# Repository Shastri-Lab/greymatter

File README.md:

# greymatter DAC controller

Embedded firmware for the Raspberry Pi Pico 2 (RP2350) controlling a multi-board DAC system for precision analog output generation. Designed for photonic neural network research applications.

## Features

- **24 DAC Control**: 8 daughter boards, each with 3 DACs (2x current, 1x voltage)
- **High Channel Count**: 112 current outputs + 32 voltage outputs = 144 total channels
- **SCPI Interface**: Standard instrument control commands over USB serial
- **Precision Output**:
  - Current: 3.125 mA to 300 mA full-scale (LTC2662)
  - Voltage: ±2.5V to ±10V bipolar, 0-10V unipolar (LTC2664)
- **16-bit Resolution**: 65,536 steps per channel
- **Fault Monitoring**: Per-DAC fault detection with interrupt support

## Hardware Requirements

- Raspberry Pi Pico 2 (RP2350)
- Greymatter motherboard with:
  - 3x MCP23S17 I/O expanders
  - TXB0106 level shifter
  - 8 daughter board slots
- Microcyte daughter boards (per slot):
  - 2x LTC2662 current DAC (5 channels each)
  - 1x LTC2664 voltage DAC (4 channels)

## Quick Start

### Prerequisites

```bash
# Set Pico SDK path
export PICO_SDK_PATH=/path/to/pico-sdk

# Required tools
# - CMake 3.13+
# - GCC ARM cross-compiler (gcc-15 recommended)
```

### Build

```bash
cd build
cmake .. -DPICO_BOARD=pico2
make picotoolBuild
C_INCLUDE_PATH= CPLUS_INCLUDE_PATH= make

# Optional: Custom SPI clock rate (default 10 MHz)
cmake .. -DPICO_BOARD=pico2 -DSPI_BAUDRATE=1000000  # 1 MHz for logic analyzer
make picotoolBuild && C_INCLUDE_PATH= CPLUS_INCLUDE_PATH= make
```

### Flash

1. Hold the **BOOTSEL** button on the Pico 2
2. Connect USB cable to computer
3. Copy `build/greymatter.uf2` to the `RPI-RP2` drive that appears
4. The Pico will reset and start running automatically

### Connect

```bash
# macOS/Linux
screen /dev/tty.usbmodem1101 115200

# Exit screen: Ctrl-A, K, Y
```

### Verify

```
*IDN?
```
Response: `greymatter,DAC Controller,001,0.1`

## Basic Usage

```bash
# Set voltage output (Board 0, DAC 2, Channel 0 to 5V)
BOARD0:DAC2:CH0:VOLT 5.0

# Set current output (Board 0, DAC 0, Channel 1 to 50mA)
BOARD0:DAC0:CH1:CURR 50.0

# Check for faults
FAULT?

# Reset all outputs
*RST
```

## Documentation

The **[user guide](docs/USER_GUIDE.md)** for the firmware contains a complete command reference, implementation details, calibration routines, and more details.

## Architecture

```
┌─────────────────────────────────────────────────────────────┐
│                     USB Serial (115200 baud)                │
└─────────────────────────────────────────────────────────────┘
                              │
                              ▼
┌─────────────────────────────────────────────────────────────┐
│                     SCPI Parser                             │
│              Command tokenization & validation              │
└─────────────────────────────────────────────────────────────┘
                              │
                              ▼
┌─────────────────────────────────────────────────────────────┐
│                     Board Manager                           │
│              Routes commands to 24 DACs                     │
└─────────────────────────────────────────────────────────────┘
                              │
              ┌───────────────┴───────────────┐
              ▼                               ▼
┌──────────────────────┐         ┌──────────────────────┐
│      LTC2662         │         │      LTC2664         │
│  Current DAC Driver  │         │  Voltage DAC Driver  │
│  (5 ch, 3-300 mA)    │         │  (4 ch, ±10V)        │
└──────────────────────┘         └──────────────────────┘
              │                               │
              └───────────────┬───────────────┘
                              ▼
┌─────────────────────────────────────────────────────────────┐
│                     SPI Manager                             │
│              Transaction coordination                       │
└─────────────────────────────────────────────────────────────┘
                              │
              ┌───────────────┴───────────────┐
              ▼                               ▼
┌──────────────────────┐         ┌──────────────────────┐
│    I/O Expanders     │         │    DAC Decoder       │
│  (MCP23S17 × 3)      │         │    (CS routing)      │
└──────────────────────┘         └──────────────────────┘
```

## Pin Assignments

| GPIO | Function | Description |
|------|----------|-------------|
| GP16 | SPI_MISO | Data from DACs/expanders |
| GP17 | SPI_CS | Chip select (expanders only) |
| GP18 | SPI_CLK | SPI clock (configurable, default 10 MHz) |
| GP19 | SPI_MOSI | Data to DACs/expanders |
| GP20 | FAULT | Combined fault input |
| GP21 | LEVEL_SHIFT_OE | Level shifter enable |
| GP22 | EXPANDER_RESET | I/O expander reset |

## Project Structure

```
greymatter/
├── main.cpp              # Entry point, USB serial loop
├── scpi_parser.*         # SCPI command parsing
├── board_manager.*       # DAC routing and management
├── spi_manager.*         # SPI peripheral control
├── io_expander.*         # MCP23S17 driver
├── dac_device.*          # Abstract DAC interface
├── ltc2662.*             # Current DAC driver
├── ltc2664.*             # Voltage DAC driver
├── utils.*               # String parsing utilities
├── CMakeLists.txt        # Build configuration
├── docs/                 # Hardware programming guides
├── README.md             # This file
└── USER_GUIDE.md         # Detailed user documentation
```

## License
This software is licensed under the MIT license found at [LICENSE](LICENSE).

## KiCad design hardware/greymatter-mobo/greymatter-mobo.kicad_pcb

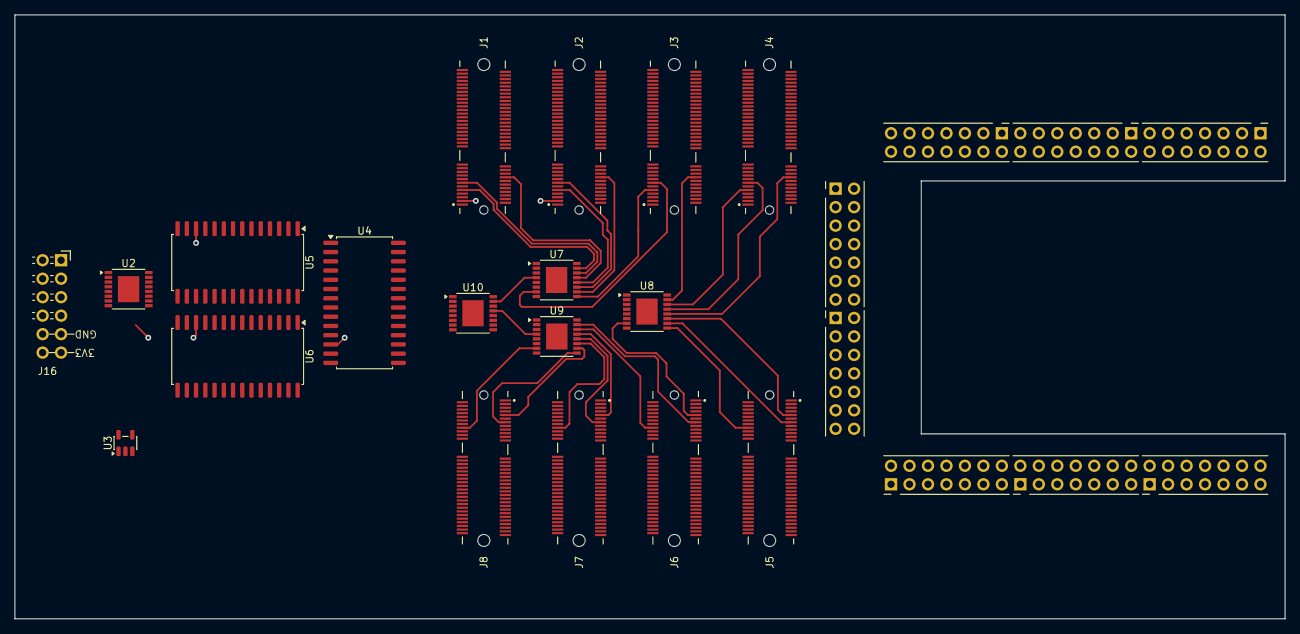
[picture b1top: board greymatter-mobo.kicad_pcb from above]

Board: 6 copper layers, 174.6 x 83.0 mm, 18 parts (0 on the bottom side), 79 nets.

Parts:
J1, J2, J3, J4, J5, J6, J7, J8: M2-J-67-V-SMT-5.30-KE-KT; ADAMTECH_M2-J-67-V-SMT-5.30-KE-KT
J16: Conn_01x12; PinHeader_2x06_PMOD_Peripheral
U2: TXB0106RGYR; TSSOP-16-1EP_4.4x5mm_P0.65mm
U3: 74LVC1G32; SOT-23-5
U4, U5, U6: MCP23S17_SO; SOIC-28W_7.5x17.9mm_P1.27mm
U7, U8, U9, U10: SN74LVC138ARGYR; TSSOP-16-1EP_4.4x5mm_P0.65mm

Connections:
+3V3: J16.6, J16.12, U2.2 (VCCA)
+5V: J1.4, J1.21, J2.4, J2.21, J3.4, J3.21, J4.4, J4.21, J5.4, J5.21, J6.4, J6.21, J7.4, J7.21, J8.4, J8.21, U2.15 (VCCB), U3.5 (VCC), U4.9 (VDD), U5.9 (VDD), U5.15 (A0), U6.9 (VDD), U6.16 (A1), U7.6 (G1), U7.16 (VCC), U8.6 (G1), U8.16 (VCC), U9.6 (G1), U9.16 (VCC), U10.16 (VCC)
+10V: J1.34, J1.35, J1.36, J1.37, J2.34, J2.35, J2.36, J2.37, J3.34, J3.35, J3.36, J3.37, J4.34, J4.35, J4.36, J4.37, J5.34, J5.35, J5.36, J5.37, J6.34, J6.35, J6.36, J6.37, J7.34, J7.35, J7.36, J7.37, J8.34, J8.35, J8.36, J8.37
-10V: J1.70, J1.71, J1.72, J1.73, J2.70, J2.71, J2.72, J2.73, J3.70, J3.71, J3.72, J3.73, J4.70, J4.71, J4.72, J4.73, J5.70, J5.71, J5.72, J5.73, J6.70, J6.71, J6.72, J6.73, J7.70, J7.71, J7.72, J7.73, J8.70, J8.71, J8.72, J8.73
CLRDAC: J1.10, J2.10, J3.10, J4.10, J5.10, J6.10, J7.10, J8.10
CS: U2.16 (B1), U4.11 (~CS), U5.11 (~CS), U6.11 (~CS), U10.6 (G1)
CS0: U4.25 (GPA4), U7.1 (A), U8.1 (A), U9.1 (A)
CS1: U4.24 (GPA3), U7.2 (B), U8.2 (B), U9.2 (B)
CS2: U4.23 (GPA2), U7.3 (C), U8.3 (C), U9.3 (C)
CS3: U4.22 (GPA1), U10.1 (A)
CS4: U4.21 (GPA0), U10.2 (B)
CS_3V3: J16.1, U2.1 (A1)
CS_11: J1.7, U7.15 (Y0)
CS_12: J1.5, U7.14 (Y1)
CS_13: J1.3, U7.13 (Y2)
CS_21: J2.7, U7.12 (Y3)
CS_22: J2.5, U7.11 (Y4)
CS_23: J2.3, U7.10 (Y5)
CS_31: J3.7, U7.9 (Y6)
CS_32: J3.5, U7.7 (Y7)
CS_33: J3.3, U8.15 (Y0)
CS_41: J4.7, U8.14 (Y1)
CS_42: J4.5, U8.13 (Y2)
CS_43: J4.3, U8.12 (Y3)
CS_51: J5.7, U8.11 (Y4)
CS_52: J5.5, U8.10 (Y5)
CS_53: J5.3, U8.9 (Y6)
CS_61: J6.7, U8.7 (Y7)
CS_62: J6.5, U9.15 (Y0)
CS_63: J6.3, U9.14 (Y1)
CS_71: J7.7, U9.13 (Y2)
CS_72: J7.5, U9.12 (Y3)
CS_73: J7.3, U9.11 (Y4)
CS_81: J8.7, U9.10 (Y5)
CS_82: J8.5, U9.9 (Y6)
CS_83: J8.3, U9.7 (Y7)
DAC_FAULT: U3.2, U5.20 (INTA)
DEN: U4.26 (GPA5), U7.5 (*G2B), U8.5 (*G2B), U9.5 (*G2B)
D_EN0: U7.4 (*G2A), U10.15 (Y0)
D_EN1: U8.4 (*G2A), U10.14 (Y1)
D_EN2: U9.4 (*G2A), U10.13 (Y2)
FAULT: U2.10 (B6), U3.4
FAULT_3V3: J16.7, U2.7 (A6)
FAULT_11: J1.19, U5.21 (GPA0)
FAULT_12: J1.18, U5.22 (GPA1)
FAULT_21: J2.19, U5.23 (GPA2)
FAULT_22: J2.18, U5.24 (GPA3)
FAULT_31: J3.19, U5.25 (GPA4)
FAULT_32: J3.18, U5.26 (GPA5)
FAULT_41: J4.19, U5.27 (GPA6)
FAULT_42: J4.18, U5.28 (GPA7)
FAULT_51: J5.19, U5.1 (GPB0)
FAULT_52: J5.18, U5.2 (GPB1)
FAULT_61: J6.19, U5.3 (GPB2)
FAULT_62: J6.18, U5.4 (GPB3)
FAULT_71: J7.19, U5.5 (GPB4)
FAULT_72: J7.18, U5.6 (GPB5)
FAULT_81: J8.19, U5.7 (GPB6)
FAULT_82: J8.18, U5.8 (GPB7)
GND: J1.1, J1.2, J1.8, J1.11, J1.13, J1.14, J1.15, J1.17, J1.22, J1.23, J1.32, J1.33, J1.38, J1.39, J1.40, J1.41, J1.44, J1.45, J1.48, J1.49, J1.52, J1.53, J1.56, J1.57, J1.60, J1.61, J1.64, J1.65, J1.68, J1.69, J1.74, J1.75, J2.1, J2.2, J2.8, J2.11, J2.13, J2.14, J2.15, J2.17, J2.22, J2.23, J2.32, J2.33, J2.38, J2.39, J2.40, J2.41, J2.44, J2.45, J2.48, J2.49, J2.52, J2.53, J2.56, J2.57, J2.60, J2.61, J2.64, J2.65, J2.68, J2.69, J2.74, J2.75, J3.1, J3.2, J3.8, J3.11, J3.13, J3.14, J3.15, J3.17, J3.22, J3.23, J3.32, J3.33, J3.38, J3.39, J3.40, J3.41, J3.44, J3.45, J3.48, J3.49, J3.52, J3.53, J3.56, J3.57, J3.60, J3.61, J3.64, J3.65, J3.68, J3.69, J3.74, J3.75, J4.1, J4.2, J4.8, J4.11, J4.13, J4.14, J4.15, J4.17, J4.22, J4.23, J4.32, J4.33, J4.38, J4.39, J4.40, J4.41, J4.44, J4.45, J4.48, J4.49, J4.52, J4.53, J4.56, J4.57, J4.60, J4.61, J4.64, J4.65, J4.68, J4.69, J4.74, J4.75, J5.1, J5.2, J5.8, J5.11, J5.13, J5.14, J5.15, J5.17, J5.22, J5.23, J5.32, J5.33, J5.38, J5.39, J5.40, J5.41, J5.44, J5.45, J5.48, J5.49, J5.52, J5.53, J5.56, J5.57, J5.60, J5.61, J5.64, J5.65, J5.68, J5.69, J5.74, J5.75, J6.1, J6.2, J6.8, J6.11, J6.13, J6.14, J6.15, J6.17, J6.22, J6.23, J6.32, J6.33, J6.38, J6.39, J6.40, J6.41, J6.44, J6.45, J6.48, J6.49, J6.52, J6.53, J6.56, J6.57, J6.60, J6.61, J6.64, J6.65, J6.68, J6.69, J6.74, J6.75, J7.1, J7.2, J7.8, J7.11, J7.13, J7.14, J7.15, J7.17, J7.22, J7.23, J7.32, J7.33, J7.38, J7.39, J7.40, J7.41, J7.44, J7.45, J7.48, J7.49, J7.52, J7.53, J7.56, J7.57, J7.60, J7.61, J7.64, J7.65, J7.68, J7.69, J7.74, J7.75, J8.1, J8.2, J8.8, J8.11, J8.13, J8.14, J8.15, J8.17, J8.22, J8.23, J8.32, J8.33, J8.38, J8.39, J8.40, J8.41, J8.44, J8.45, J8.48, J8.49, J8.52, J8.53, J8.56, J8.57, J8.60, J8.61, J8.64, J8.65, J8.68, J8.69, J8.74, J8.75, J16.5, J16.11, U2.9 (GND), U2.17 (EPAD), U3.3 (GND), U4.10 (VSS), U4.15 (A0), U4.16 (A1), U4.17 (A2), U5.10 (VSS), U5.16 (A1), U5.17 (A2), U6.10 (VSS), U6.15 (A0), U6.17 (A2), U7.8 (GND), U7.17 (EPAD), U8.8 (GND), U8.17 (EPAD), U9.8 (GND), U9.17 (EPAD), U10.3 (C), U10.4 (*G2A), U10.5 (*G2B), U10.8 (GND), U10.17 (EPAD)
LDAC: J1.16, J2.16, J3.16, J4.16, J5.16, J6.16, J7.16, J8.16, U4.1 (GPB0)
MISO: J1.6, J2.6, J3.6, J4.6, J5.6, J6.6, J7.6, J8.6, U2.12 (B4), U4.14 (SO), U5.14 (SO), U6.14 (SO)
MISO_3V3: J16.3, U2.5 (A4)
MOSI: J1.9, J2.9, J3.9, J4.9, J5.9, J6.9, J7.9, J8.9, U2.13 (B3), U4.13 (SI), U5.13 (SI), U6.13 (SI)
MOSI_3V3: J16.2, U2.4 (A3)
OE_3V3: J16.9, U2.8 (OE)
RESET: U2.11 (B5), U4.18 (~RESET), U5.18 (~RESET), U6.18 (~RESET)
RESET_3V3: J16.8, U2.6 (A5)
SCK_3V3: J16.4, U2.3 (A2)
SCLK: J1.12, J2.12, J3.12, J4.12, J5.12, J6.12, J7.12, J8.12, U2.14 (B2), U4.12 (SCK), U5.12 (SCK), U6.12 (SCK)
TEMP1: J1.20, U6.21 (GPA0)
TEMP2: J2.20, U6.22 (GPA1)
TEMP3: J3.20, U6.23 (GPA2)
TEMP4: J4.20, U6.24 (GPA3)
TEMP5: J5.20, U6.25 (GPA4)
TEMP6: J6.20, U6.26 (GPA5)
TEMP7: J7.20, U6.27 (GPA6)
TEMP8: J8.20, U6.28 (GPA7)
TEMP_FAULT: U3.1, U6.20 (INTA)

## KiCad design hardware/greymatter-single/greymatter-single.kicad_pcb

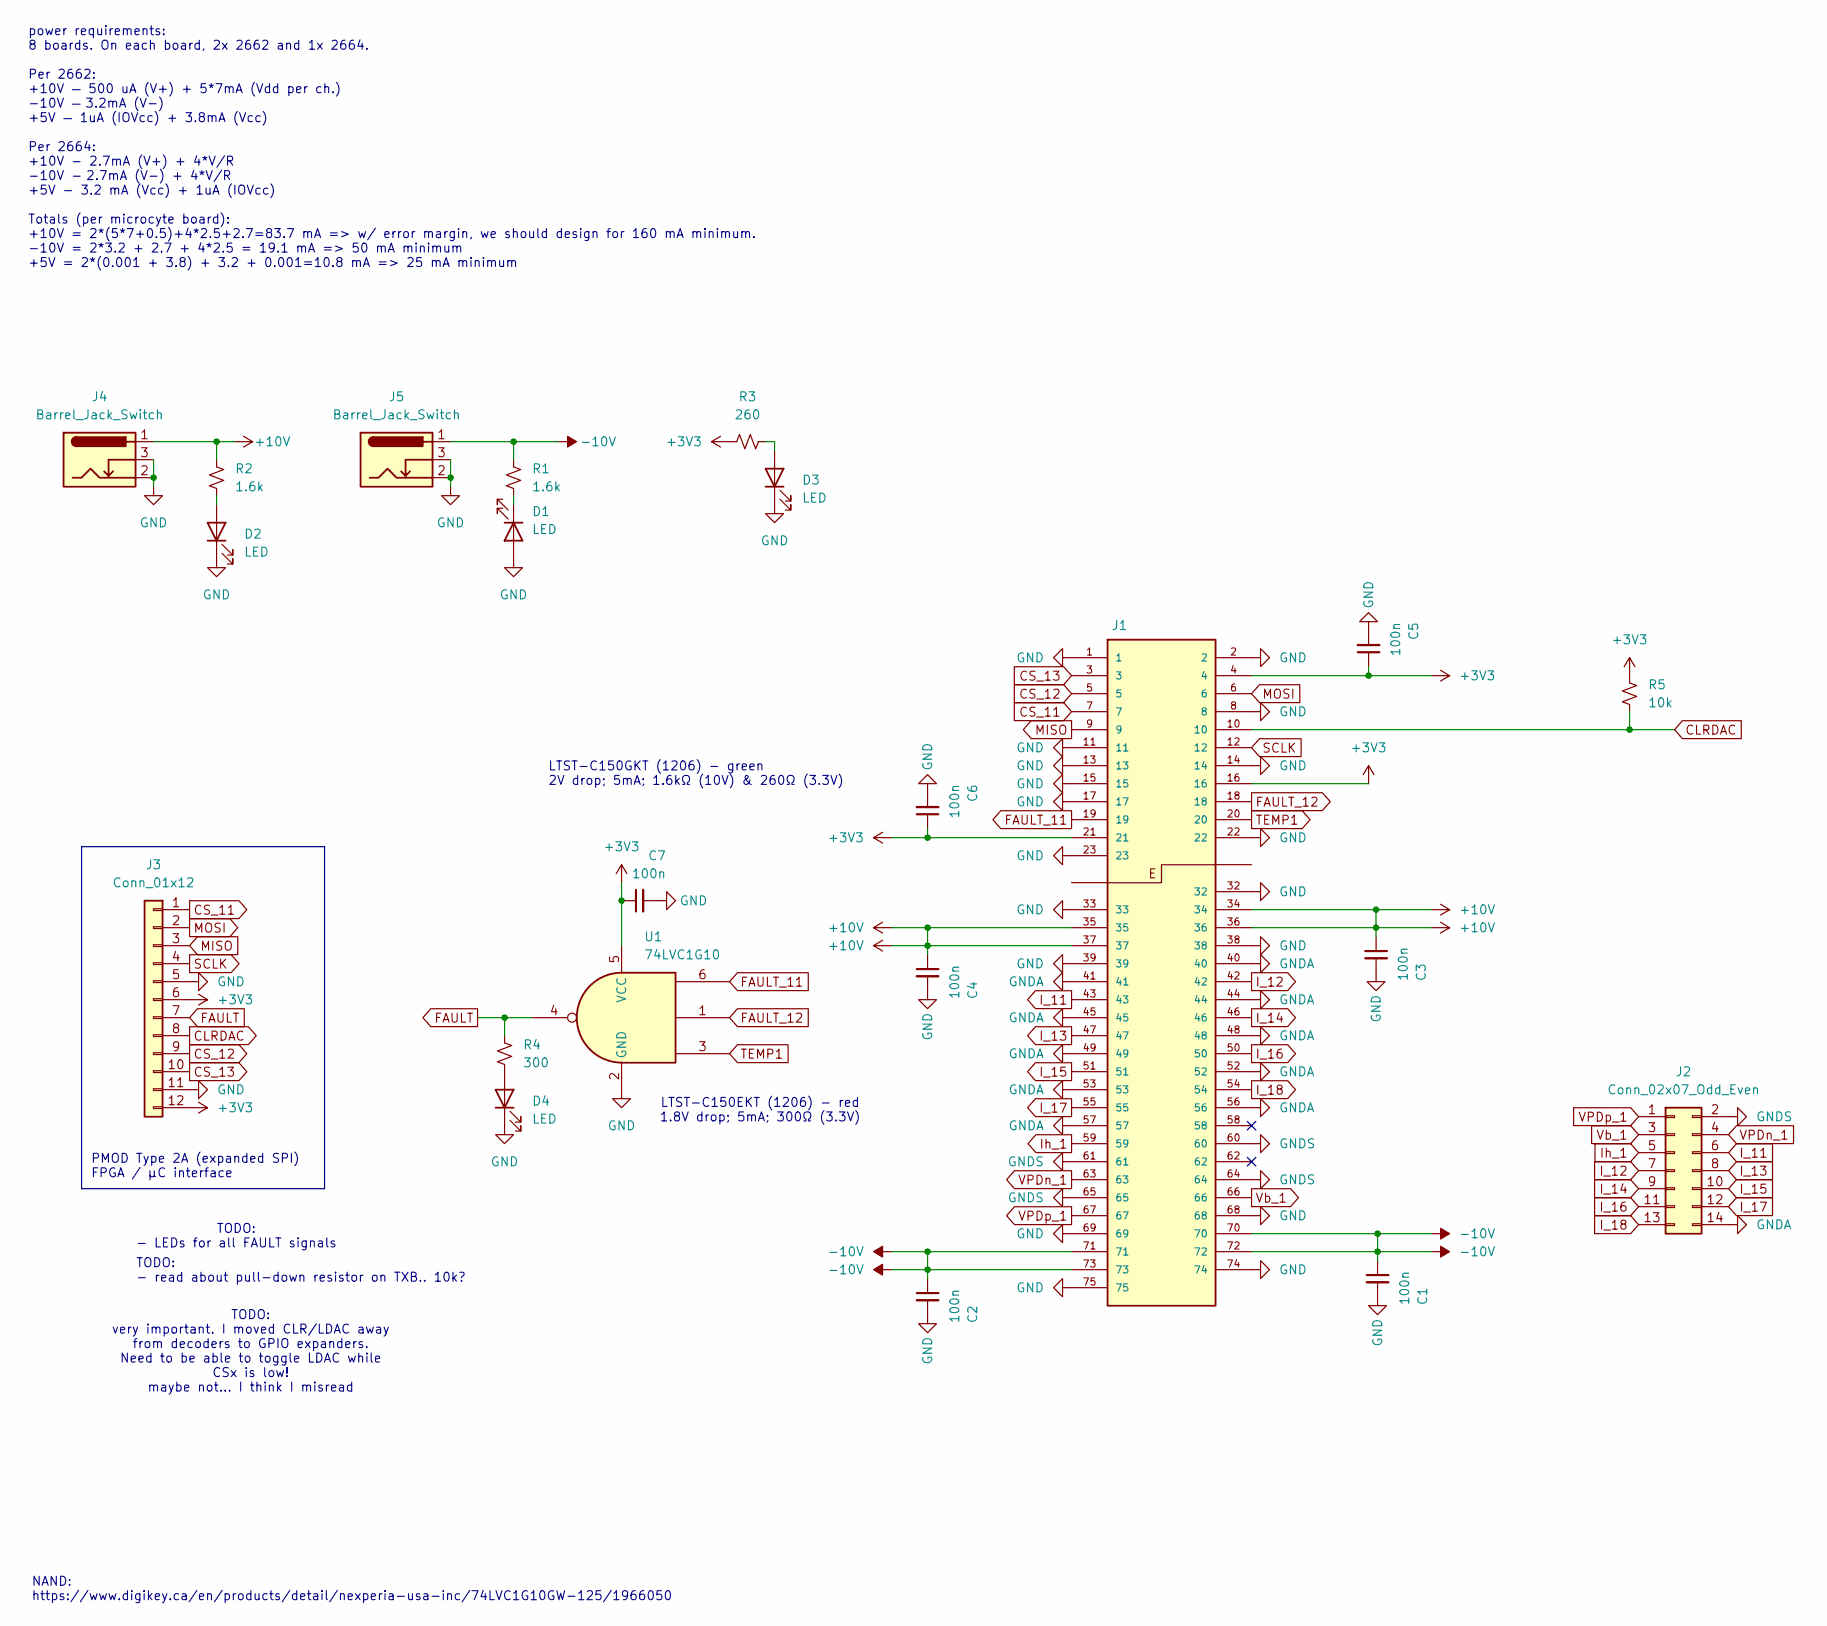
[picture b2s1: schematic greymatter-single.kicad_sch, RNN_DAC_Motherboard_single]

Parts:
C1, C2, C3, C4, C5, C6, C7: 100n; C_1206_3216Metric
D1, D2, D3, D4: LED; D_1206_3216Metric
J1: M2-J-67-V-SMT-5.30-KE-KT; ADAMTECH_M2-J-67-V-SMT-5.30-KE-KT; PARTREV 2
J2: Conn_02x07_Odd_Even; PinSocket_2x07_P2.54mm_Vertical
J3: Conn_01x12; PinHeader_2x06_PMOD_Peripheral_Vertical
J4, J5: Barrel_Jack_Switch; CUI_PJ-044A
R1, R2: 1.6k; R_1206_3216Metric
R3: 260; R_1206_3216Metric
R4: 300; R_1206_3216Metric
R5: 10k; R_1206_3216Metric
U1: 74LVC1G10; SOT-457T

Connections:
+3V3: C5.1, C6.1, C7.1, J1.4, J1.16, J1.21, J3.6, J3.12, R3.1, R5.2, U1.5 (VCC)
+10V: C3.1, C4.1, J1.34, J1.35, J1.36, J1.37, J4.1, R2.1
-10V: C1.1, C2.1, J1.70, J1.71, J1.72, J1.73, J5.1, R1.1
CLRDAC: J1.10, J3.8, R5.1
CS_11: J1.7, J3.1
CS_12: J1.5, J3.9
CS_13: J1.3, J3.10
FAULT: J3.7, R4.2, U1.4
FAULT_11: J1.19, U1.6
FAULT_12: J1.18, U1.1
GND: C1.2, C2.2, C3.2, C4.2, C5.2, C6.2, C7.2, D1.2 (A), D2.1 (K), D3.1 (K), D4.1 (K), J1.1, J1.2, J1.8, J1.11, J1.13, J1.14, J1.15, J1.17, J1.22, J1.23, J1.32, J1.33, J1.38, J1.39, J1.68, J1.69, J1.74, J1.75, J3.5, J3.11, J4.2, J4.3, J5.2, J5.3, U1.2 (GND)
GNDA: J1.40, J1.41, J1.44, J1.45, J1.48, J1.49, J1.52, J1.53, J1.56, J1.57, J2.14
GNDS: J1.60, J1.61, J1.64, J1.65, J2.2
I_11: J1.43, J2.6
I_12: J1.42, J2.7
I_13: J1.47, J2.8
I_14: J1.46, J2.9
I_15: J1.51, J2.10
I_16: J1.50, J2.11
I_17: J1.55, J2.12
I_18: J1.54, J2.13
Ih_1: J1.59, J2.5
MISO: J1.9, J3.3
MOSI: J1.6, J3.2
unnamed: D1.1 (K), R1.2
unnamed: D2.2 (A), R2.2
unnamed: D3.2 (A), R3.2
unnamed: D4.2 (A), R4.1
SCLK: J1.12, J3.4
TEMP1: J1.20, U1.3
VPDn_1: J1.63, J2.4
VPDp_1: J1.67, J2.1
Vb_1: J1.66, J2.3

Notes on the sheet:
LTST-C150GKT (1206) - green 2V drop; 5mA; 1.6kΩ (10V) & 260Ω (3.3V)
PMOD Type 2A (expanded SPI) FPGA / µC interface
TODO: very important. I moved CLR/LDAC away from decoders to GPIO expanders. Need to be able to toggle LDAC while CSx is low! maybe not... I think I misread
TODO: - read about pull-down resistor on TXB.. 10k?
NAND: https://www.digikey.ca/en/products/detail/nexperia-usa-inc/74LVC1G10GW-125/1966050
LTST-C150EKT (1206) - red 1.8V drop; 5mA; 300Ω (3.3V)
TODO: - LEDs for all FAULT signals
power requirements: 8 boards. On each board, 2x 2662 and 1x 2664. Per 2662: +10V — 500 uA (V+) + 5*7mA (Vdd per ch.) -10V — 3.2mA (V-) +5V — 1uA (IOVcc) + 3.8mA (Vcc) Per 2664: +10V - 2.7mA (V+) + 4*V/R -10V - 2.7mA (V-) + 4*V/R +5V - 3.2 mA (Vcc) + 1uA (IOVcc) Totals (per microcyte board): +10V = 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

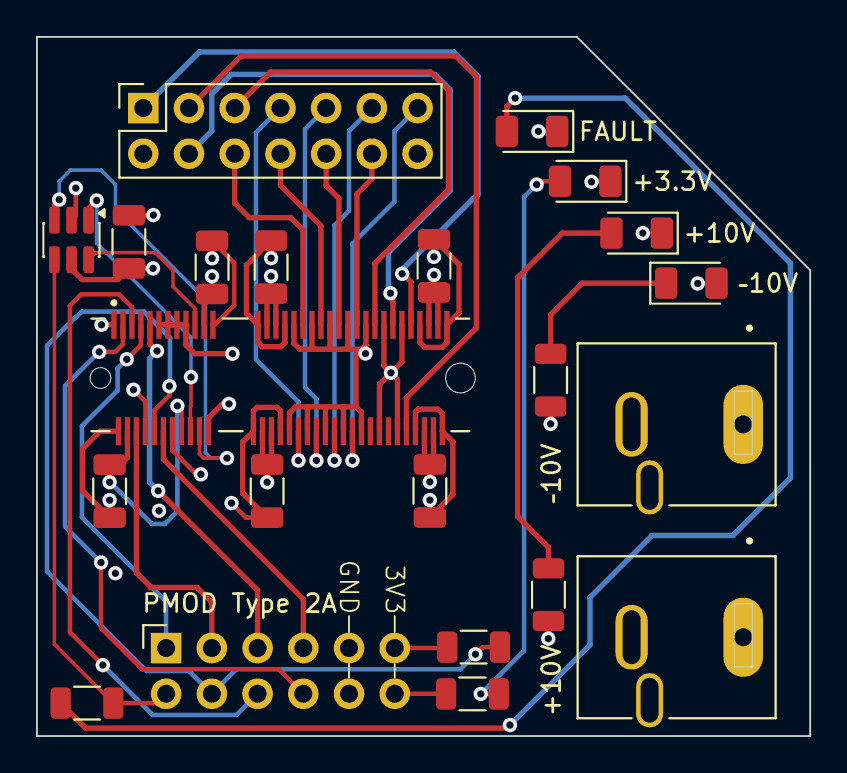
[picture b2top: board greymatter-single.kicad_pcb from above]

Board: 4 copper layers, 43.0 x 38.8 mm, 22 parts (0 on the bottom side), 33 nets.

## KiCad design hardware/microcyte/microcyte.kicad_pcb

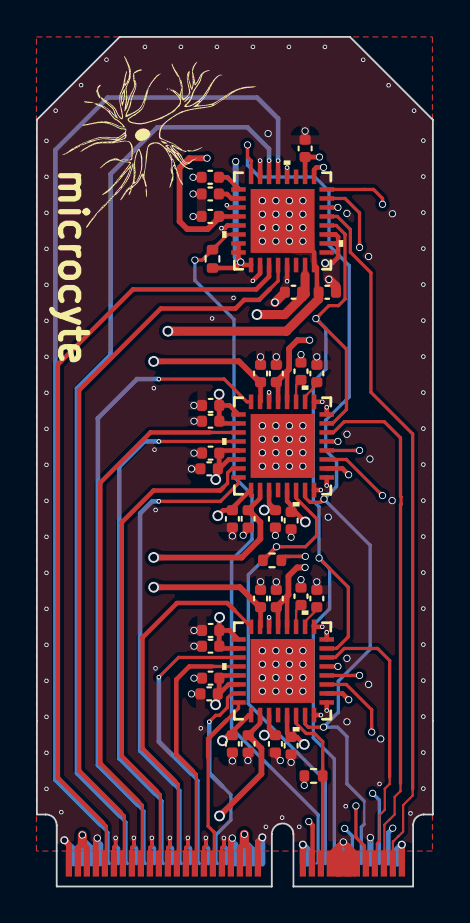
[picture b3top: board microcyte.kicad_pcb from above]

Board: 6 copper layers, 22.0 x 47.2 mm, 37 parts (0 on the bottom side), 35 nets.

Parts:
C1, C3, C5: 47n; C_0402_1005Metric
C2, C4, C6, C16, C26, C29: 100n; C_0402_1005Metric
C7, C8, C9, C10, C11, C12, C13, C14, C15, C17, C18, C19, C20, C21, C22, C23, C24, C25, C27, C28, C30: 1u; C_0402_1005Metric
J1: Conn_02x38_Odd_Even; Connector_M.2_key-E
R1, R3, R5: 10k; R_0402_1005Metric
U1, U2: LTC2662HUH-12-PBF; 05-08-1693_ADI
U3: LTC2664HUH-12-PBF; 05-08-1693_ADI

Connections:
+5V: C15.1, C16.1, C25.1, C26.1, C29.1, C30.1, J1.4, J1.21, R1.1, R3.1, R5.1, U1.2 (TGP), U1.12 (FSADJ), U1.13 (VCC), U1.29 (IOVCC), U2.2 (TGP), U2.12 (FSADJ), U2.13 (VCC), U2.29 (IOVCC), U3.1 (MSP2), U3.17 (TGP), U3.18 (IOVCC), U3.28 (VCC), U3.31 (MSP0), U3.32 (MSP1)
+10V: C7.1, C8.1, C9.1, C10.1, C11.1, C12.1, C17.1, C18.1, C19.1, C20.1, C21.1, C22.1, C27.1, J1.34, J1.35, J1.36, J1.37, U1.17 (VDD4), U1.18 (VDD3), U1.21 (VDD2), U1.22 (VDD1), U1.25 (VDD0), U1.27 (V+), U2.17 (VDD4), U2.18 (VDD3), U2.21 (VDD2), U2.22 (VDD1), U2.25 (VDD0), U2.27 (V+), U3.7 (V+)
-10V: C13.1, C14.1, C23.1, C24.1, C28.1, J1.70, J1.71, J1.72, J1.73, U1.15 (V-), U1.26 (V-), U2.15 (V-), U2.26 (V-), U3.8 (V), U3.33 (EPAD)
CLR: J1.10, U1.31 (*CLR), U2.31 (*CLR), U3.24 (*CLR)
FAULT1: J1.19, R3.2, U1.30 (*FAULT)
FAULT2: J1.18, R1.2, U2.30 (*FAULT)
GND: C1.2, C2.2, C3.2, C4.2, C5.2, C6.2, C7.2, C8.2, C9.2, C10.2, C11.2, C12.2, C13.2, C14.2, C15.2, C16.2, C17.2, C18.2, C19.2, C20.2, C21.2, C22.2, C23.2, C24.2, C25.2, C26.2, C27.2, C28.2, C29.2, C30.2, J1.1, J1.2, J1.8, J1.11, J1.13, J1.14, J1.15, J1.17, J1.22, J1.23, J1.32, J1.33, J1.38, J1.39, J1.40, J1.41, J1.44, J1.45, J1.48, J1.49, J1.52, J1.53, J1.56, J1.57, J1.60, J1.61, J1.64, J1.65, J1.68, J1.69, J1.74, J1.75, U1.1 (GND), U1.8 (GND), U1.9 (REFLO), U1.14 (GND), U1.32 (GND), U1.33 (GND), U2.1 (GND), U2.8 (GND), U2.9 (REFLO), U2.14 (GND), U2.32 (GND), U2.33 (GND), U3.2 (MUXIN0), U3.5 (MUXIN1), U3.10 (REFLO), U3.11 (GND), U3.20 (MUXIN2), U3.23 (MUXIN3), U3.27 (REFLO), U3.29 (GND)
I0: J1.43, U1.24 (OUT0)
I1: J1.42, U1.23 (OUT1)
I2: J1.47, U1.20 (OUT2)
I3: J1.46, U1.19 (OUT3)
I4: J1.51, U1.16 (OUT4)
I5: J1.50, U2.24 (OUT0)
I6: J1.55, U2.23 (OUT1)
I7: J1.54, U2.20 (OUT2)
I8: J1.59, U2.19 (OUT3)
I9: J1.58, U2.16 (OUT4)
LDAC: J1.16, U1.7 (*LDAC), U2.7 (*LDAC), U3.12 (*LDAC)
MISO: J1.9, U1.4 (SDO), U2.4 (SDO), U3.15 (SDO)
MOSI: J1.6, U1.3 (SDI), U2.3 (SDI), U3.16 (SDI)
unnamed: C3.1, U1.10 (REF)
unnamed: C4.1, U1.11 (REFCOMP)
unnamed: C5.1, U2.10 (REF)
unnamed: C6.1, U2.11 (REFCOMP)
unnamed: C1.1, U3.25 (REF)
unnamed: C2.1, U3.26 (REFCOMP)
SCLK: J1.12, U1.5 (SCK), U2.5 (SCK), U3.14 (SCK)
SS1: J1.7, U1.6 (*CS/LD)
SS2: J1.5, U2.6 (*CS/LD)
SS3: J1.3, U3.13 (*CS/LD)
TEMP: J1.20, R5.2, U3.30 (*OVRTMP)
Vb0: J1.67, U3.3 (VOUT0)
Vb1: J1.63, U3.4 (VOUT1)
Vb2: J1.66, U3.21 (VOUT2)
Vb3: J1.62, U3.22 (VOUT3)

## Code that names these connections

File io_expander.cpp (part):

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    // Step 2: Now configure each expander individually
    // Expander 0: Control signals
    //   Port A: CS0-CS4 (pins 4-0), D_EN (pin 5) - all outputs
    //   Port B: LDAC (pin 0), CLR (pin 7) - outputs; other pins unused
    init_expander(EXPANDER_ADDR::EXPANDER_0,
                  0x00,  // IODIRA: all outputs (CS4-CS0 on pins 0-4, D_EN on pin 5)
                  0x00,  // IODIRB: all outputs (LDAC on pin 0, CLR on pin 7)
                  0x00,  // No interrupts on Port A
                  0x00,  // No interrupts on Port B
                  0x00,  // DEFVALA (not used for outputs)
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        ((1 << SIGNAL_MAP::LDAC_BIT) | (1 << SIGNAL_MAP::CLR_BIT)) << 8;

    // Expander 1: LTC2662 fault inputs (current DACs)
    //   Port A: Boards 0-3, DACs 0-1 (pins 0-7 = FAULT_11, FAULT_12, FAULT_21, ...)
    //   Port B: Boards 4-7, DACs 0-1 (pins 0-7 = FAULT_51, FAULT_52, FAULT_61, ...)
    init_expander(EXPANDER_ADDR::EXPANDER_1,
                  0xFF,  // IODIRA: all inputs
                  0xFF,  // IODIRB: all inputs
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
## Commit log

2025-12-26 v0 software implementation
2025-12-26 added MIT license
2025-12-27 added debugging mode
2025-12-27 added PDF docs
2025-12-27 greymatter user guide
2025-12-28 moved user guide to docs
2025-12-28 support for 12- and 16-bit resolution DACs
2025-12-28 specified hardware pin mappings for I/O expander
2025-12-28 support for DAC calibration
2025-12-28 fixed DEBUG:STEP mode
2026-02-04 added mode for single microcyte board (no I/O expander)
2026-02-04 untracked cache
2026-02-04 removed debug mode; use configurable clock rate
2026-02-04 updated user guide for recent edits
2026-02-04 flush garbage characters from serial before accepting any commands
2026-02-04 change default DAC span
2026-02-04 set_span_all command should use the correct SPI command
2026-02-05 fixed SPI vs. GPIO init order
2026-02-05 updated README and user guide
2026-02-05 reorganized project structure
2026-02-05 12-bit data word fix
2026-02-05 append to previous commit
2026-02-05 docs fixes
2026-02-05 FAULT pin is push-pull not active-low
2026-02-05 added more pdfs
2026-02-05 test waveforms for SPI logic
2026-02-05 untracked notes
2026-02-05 forgot to return code in current to code function
2026-02-06 python driver
2026-02-06 implemented setting span on single channel
2026-02-08 added echo readback function
2026-02-09 added testing files
2026-02-10 moved all code to software directory to make make room for hardware
2026-02-10 RPi Pico PMOD PCB
2026-02-10 microcyte DAC PCB
2026-02-10 greymatter-single PCB
2026-02-10 ignored KiCAD files
2026-02-10 progress on full 8x8 motherboard PCB
2026-02-13 added host controller
2026-02-13 fixed python project pip install
2026-02-16 serial numbers for controller to identify from software
2026-02-16 pico 2 has 4MB flash
